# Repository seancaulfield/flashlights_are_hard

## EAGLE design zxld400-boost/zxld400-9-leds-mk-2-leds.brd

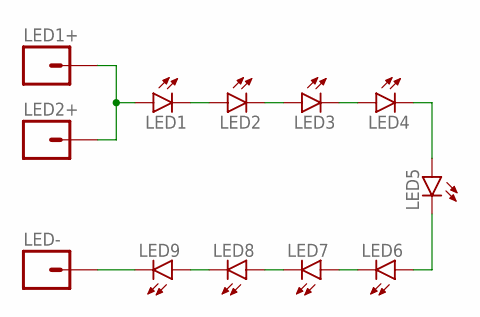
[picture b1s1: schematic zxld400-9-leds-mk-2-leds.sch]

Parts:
LED1, LED2, LED3, LED4, LED5, LED6, LED7, LED8, LED9: LED5MM_SHORTPADS
LED1+, LED2+: M01PTH; 1X01
LED-: M01PTH; 1X01

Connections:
unnamed: LED1.A, LED1+.1, LED2+.1
unnamed: LED9.K (C), LED-.1
unnamed: LED1.K (C), LED2.A
unnamed: LED2.K (C), LED3.A
unnamed: LED3.K (C), LED4.A
unnamed: LED4.K (C), LED5.A
unnamed: LED5.K (C), LED6.A
unnamed: LED6.K (C), LED7.A
unnamed: LED7.K (C), LED8.A
unnamed: LED8.K (C), LED9.A

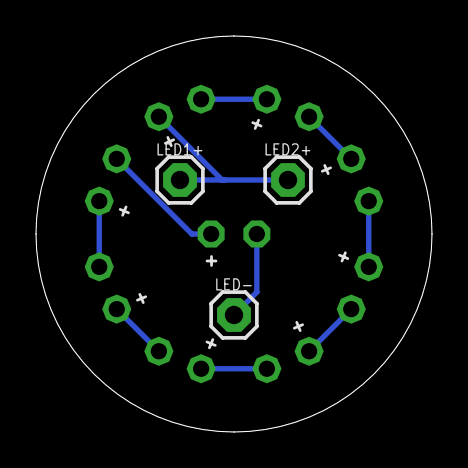
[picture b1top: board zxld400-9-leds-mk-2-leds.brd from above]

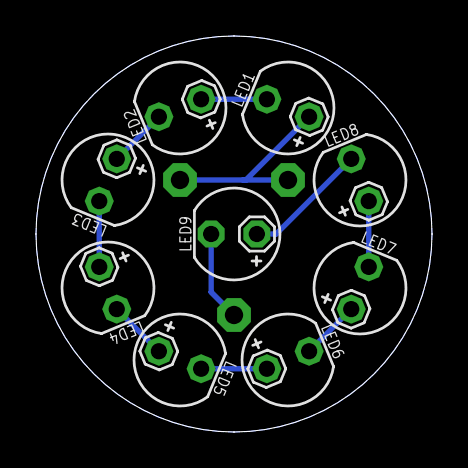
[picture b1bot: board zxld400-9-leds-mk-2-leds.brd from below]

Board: 2 copper layers, 22.0 x 22.0 mm, 12 parts (9 on the bottom side), 10 nets.
